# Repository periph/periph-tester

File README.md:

Periph-Tester Board
===================

The periph-tester board is a small PCB used to test the https://periph.io/x/periph
hardware device interface library.

The board allows simple testing of i2c, spi, 1-wire, pwm, and analog.
- Gpio can be tested by connecting two pins (preferably interrupt-capable) outside the board.
- I2C can be tested by exercising an i2c eeprom and the i2c to 1-wire interface chip.
- SPI can be tested by exercising an spi eeprom.
- 1-wire can be tested be exercising a 1-wire eeprom and a 1-wire temperature sensor.
- PWM and ADC can be tested by outputting waveforms with varying duty cycles and reading the level of a low-pass filter.
- A gpio pin is connected to the write-enable of the I2C and SPI eeproms and can be used to
  simulate certain errors by write-protecting the eeproms. (In hindsight this creates more pain
  in ensuring the pin is set correctly than it has true value...)

Standard pin-outs
-----------------
The recommended pin-outs for various platforms are as follows.

| Function | Raspberry Pi | C.H.I.P.                      | ODROID-C1                 |
| -------- | ------------ | ----------------------------- | ------------------------- |
| i2c bus  | pins 3&5     | TWI1 (bus 1)<br>pins U13 9&11 | i2ca (bus 1)<br>pins 3&5  |
| spi bus  | pins 19,21,23,24 | bus 32766<br>pins U14 27-30   | bus 0<br>pins 19,21,23,24 |
| wr-en    | pin 7        | csid0(132)<br>pin U14-31      | gpio83<br>pin 7           |
| LED      | pin 31       | csid1(133)<br>pin U14-32      | gpio100<br>pin 31         |
| PWM      |              | pwm0(34)<br>pin U13-18        | gpio108<br>pin 33         |
| ADC      | N/C          | lradc<br>pin U14-11           | adc.ain1<br>pin 37        |
| GPIO     |              | xio-p6&p7<br>pins U14-19&20<br>ap-eint1&ap-eint3<br>pins U14-23&24 |                           |

Usage
-----

### CHIP
To enable SPI, see http://www.chip-community.org/index.php/Hardware_Information
- gpio-write 133 1
- periph-smoketest -v i2c-testboard -bus 1 -wc 132
- periph-smoketest -v spi-testboard -wp 132
- periph-smoketest -v onewire-testboard -i2cbus 1
- periph-smoketest -v gpio 1019 1020
- periph-smoketest -v gpio 35 193
- gpio-write 133 0

### ODROID-C1
- periph-smoketest -v i2c-testboard -bus 2 -wc 83
- periph-smoketest -v spi-testboard -wp 83
- periph-smoketest -v onewire-testboard -i2cbus 1
- periph-smoketest -v gpio 104 115

## Raspberry Pi
- periph-smoketest -v i2c-testboard -bus 1 -wc 4
- periph-smoketest -v spi-testboard -wp 4
- periph-smoketest -v onewire-testboard -i2cbus 1
- periph-smoketest -v gpio 22 23

PCB and Parts
-------------
The PCB can be [ordered from OSH park](https://oshpark.com/shared_projects/Lhlb9MeB),
3 PCBs cost $3.75 incl shipping.
Parts can be ordered from digikey:
- M24C08 (i2c eeprom): 497-15752-1-ND
- M95080 (spi eeprom): 497-8683-1-ND
- DS2483 (i2c 1-wire interface): DS2483R+TCT-ND
- DS2431 (1-wire eeprom): DS2431+-ND
- MAX31820 (1-wire temp sensor): MAX31820MCR+-ND
- TVS diode: CDSOD323-T03SCT-ND
- LED:
- 1.8v Zener: MMSZ4678-TPMSCT-ND
- 4.7uF cap:
- 100uF cap, 4.7k resistors, 2.2k resistor: all std 0603 parts

Total parts cost: ~$10.
If you are contributing to periph and would like
an assembled board, contact the author.

Author
------
Thorsten von Eicken

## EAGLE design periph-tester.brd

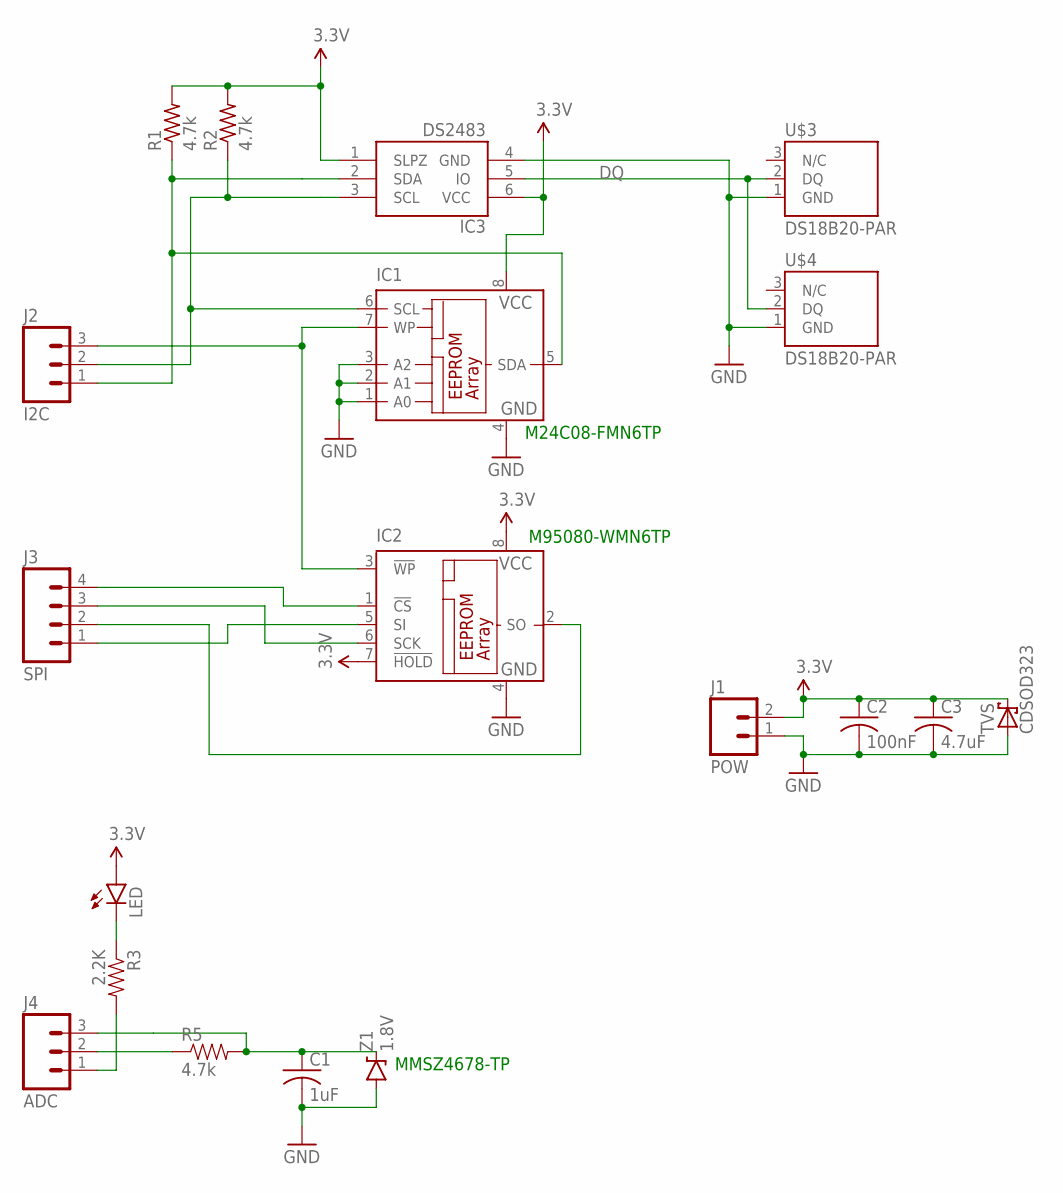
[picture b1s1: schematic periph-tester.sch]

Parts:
C1: 1uF; C0603K
C2: 100nF; C0603K
C3: 4.7uF; C0805K
IC1: 24C04SN; SO-08
IC2: 25C080SN; SO-08
IC3: DS2483; SOT23-6
J1: POW; 1X02
J2: I2C; 1X03
J3: SPI; 1X04
J4: ADC; 1X03
LED: LED0603; LED-0603
R1, R2: 4.7k; R0603
R3: 2.2K; 0603-RES
R5: 4.7k; 0603-RES
TVS: CDSOD323; SOD323-W
U$3, U$4: DS18B20-PAR; TO-92
Z1: 1.8V; SOD-123

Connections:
3.3V: C2.1, C3.1, IC1.8 (VCC), IC2.7 (!HOLD), IC2.8 (VCC), IC3.1 (SLPZ), IC3.6 (VCC), J1.2, LED.A, R1.2, R2.2, TVS.C
DQ: IC3.5 (IO), U$3.2 (DQ), U$4.2 (DQ)
GND: C1.2, C2.2, C3.2, IC1.1 (A0), IC1.2 (A1), IC1.3 (A2), IC1.4 (GND), IC2.4 (GND), IC3.4 (GND), J1.1, TVS.A, U$3.1 (GND), U$4.1 (GND), Z1.A
unnamed: IC1.6 (SCL), IC3.3 (SCL), J2.2, R2.1
unnamed: LED.C, R3.1
unnamed: IC1.5 (SDA), IC3.2 (SDA), J2.1, R1.1
unnamed: IC2.5 (SI), J3.1
unnamed: IC2.6 (SCK), J3.3
unnamed: IC2.2 (SO), J3.2
unnamed: IC2.1 (!CS), J3.4
unnamed: J4.1, R3.2
unnamed: IC1.7 (WP), IC2.3 (!WP), J2.3
unnamed: J4.2, R5.1
unnamed: C1.1, J4.3, R5.2, Z1.C

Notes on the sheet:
MMSZ4678-TP
M24C08-FMN6TP
M95080-WMN6TP

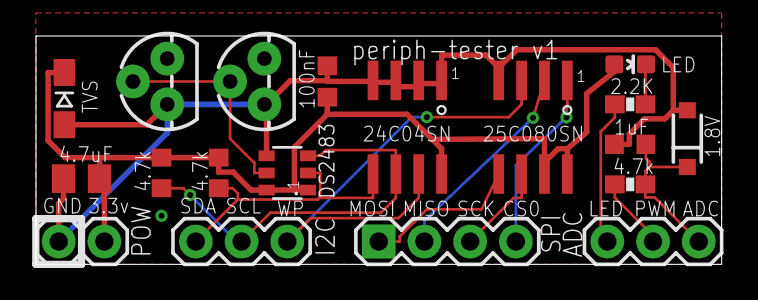
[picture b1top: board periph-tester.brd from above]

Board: 2 copper layers, 38.1 x 12.7 mm, 19 parts (0 on the bottom side), 14 nets.

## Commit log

2016-12-10 Initial periph-tester board commit
2016-12-10 fix image in readme
2016-12-14 Add LICENSE
2017-03-02 Tweak README
2017-03-02 add rPi pins
2017-03-02 fix URL

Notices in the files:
parts and their libraries:
SparkFun-Passives: Licensing: Creative Commons ShareAlike 4.0 International - https://creativecommons.org/licenses/by-sa/4.0
